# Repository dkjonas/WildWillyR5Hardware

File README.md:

Schematic and board layout for the R5 version of my robot.

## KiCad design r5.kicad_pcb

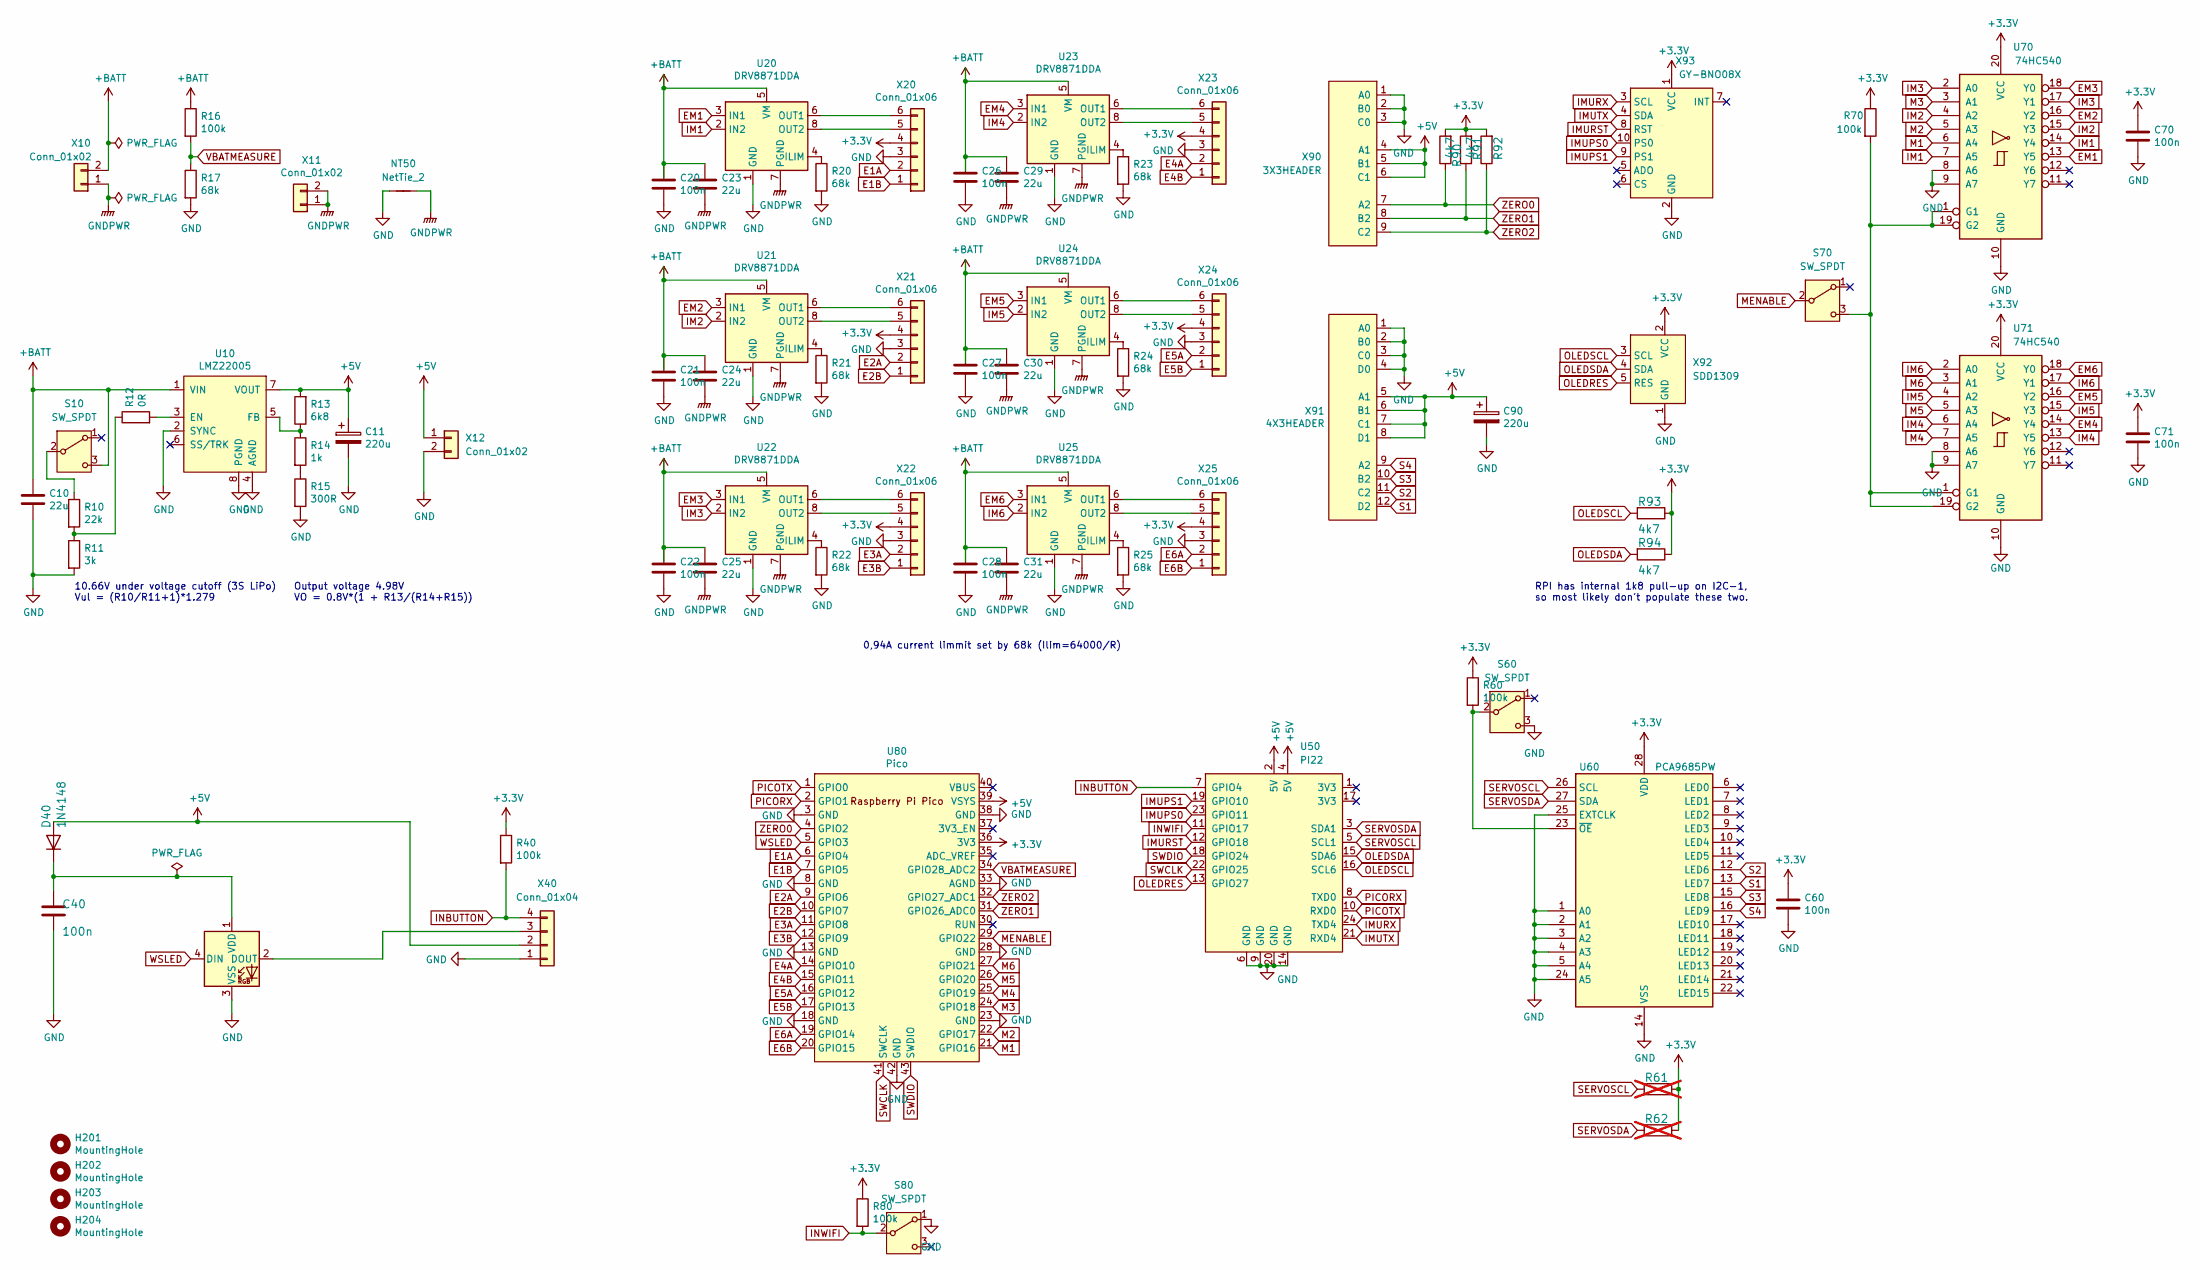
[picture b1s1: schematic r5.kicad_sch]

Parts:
C10, C23, C24, C25, C29, C30, C31: 22u; C_1206_3216Metric; LCSC Part # C12891
C11, C90: 220u; CP_Elec_6.3x7.7; LCSC Part # C970695
C20, C21, C22, C26, C27, C28, C40, C60, C70, C71: 100n; C_0805_2012Metric; LCSC Part # C49678
D40: 1N4148; D_SOD-323; LCSC Part # C2128
D41: WS2812B5050; LED_WS2812B_PLCC4_5.0x5.0mm_P3.2mm
H201, H202, H203, H204: MountingHole; MountingHole_3.2mm_M3
NT50: NetTie_2; NetTie-2_SMD_Pad2.0mm
R10: 22k; R_0805_2012Metric; LCSC Part # C17560
R11: 3k; R_0805_2012Metric; LCSC Part # C17661
R12: 0R; R_0805_2012Metric; LCSC Part # C17477
R13: 6k8; R_0805_2012Metric; LCSC Part # C17772
R14: 1k; R_0805_2012Metric; LCSC Part # C17513
R15: 300R; R_0805_2012Metric; LCSC Part # C17617
R16, R40, R60, R70, R80: 100k; R_0805_2012Metric; LCSC Part # C149504
R17, R20, R21, R22, R23, R24, R25: 68k; R_0805_2012Metric; LCSC Part # C17801
R61, R62: R_0805_2012Metric; not fitted
R90, R91, R92, R93, R94: 4k7; R_0805_2012Metric; LCSC Part # C17673
S10, S60, S70, S80: SW_SPDT; SW_Slide_1P2T_CK_OS102011MS2Q
U10: LMZ22005; 7TO-PMOD; LCSC Part # C2865843
U20, U21, U22, U23, U24, U25: DRV8871DDA; Texas_HTSOP-8-1EP_3.9x4.9mm_P1.27mm_EP2.95x4.9mm_Mask2.4x3.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; JLCPCB Rotation Offset -90
U50: PI22; PinSocket_2x12_P2.54mm_Vertical
U60: PCA9685PW; TSSOP-28_4.4x9.7mm_P0.65mm; LCSC Part # C2678753
U70, U71: 74HC540; TSSOP-20_4.4x6.5mm_P0.65mm; LCSC Part # C2682166
U80: Pico; RaspberryPiPico_SMD
X10: Conn_01x02; AMASS_XT60PW-M
X11: Conn_01x02; PinHeader_1x02_P2.54mm_Vertical
X12: Conn_01x02; JST_PH_B2B-PH-K_1x02_P2.00mm_Vertical
X20, X21, X22, X23, X24, X25: Conn_01x06; JST_PH_B6B-PH-K_1x06_P2.00mm_Vertical
X40: Conn_01x04; PinHeader_1x04_P2.54mm_Vertical
X90: 3X3HEADER; PinHeader_3x03_P2.54mm_Vertical
X91: 4X3HEADER; PinHeader_3x04_P2.54mm_Vertical
X92: SDD1309; PinHeader_1x05_P2.54mm_Vertical
X93: GY-BNO08X

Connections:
+3.3V: C60.1, C70.1, C71.1, R40.1, R60.1, R61.1, R62.1, R70.1, R80.1, R90.2, R91.2, R92.2, R93.1, R94.1, U60.28 (VDD), U70.20 (VCC), U71.20 (VCC), U80.36 (3V3), X20.4, X21.4, X22.4, X23.4, X24.4, X25.4, X92.2 (VCC), X93.1 (VCC)
+5V: C11.1, C90.1, D40.2 (A), R13.2, U10.7 (VOUT), U50.2 (5V), U50.4 (5V), U80.39 (VSYS), X12.1, X40.2, X90.4 (A1), X90.5 (B1), X90.6 (C1), X91.5 (A1), X91.6 (B1), X91.7 (C1), X91.8 (D1)
+BATT: C10.1, C20.1, C21.1, C22.1, C23.1, C24.1, C25.1, C26.1, C27.1, C28.1, C29.1, C30.1, C31.1, R16.1, S10.3 (C), U10.1 (VIN), U20.5 (VM), U21.5 (VM), U22.5 (VM), U23.5 (VM), U24.5 (VM), U25.5 (VM), X10.2
E1A: U80.6 (GPIO4), X20.2
E1B: U80.7 (GPIO5), X20.1
E2A: U80.9 (GPIO6), X21.2
E2B: U80.10 (GPIO7), X21.1
E3A: U80.11 (GPIO8), X22.2
E3B: U80.12 (GPIO9), X22.1
E4A: U80.14 (GPIO10), X23.2
E4B: U80.15 (GPIO11), X23.1
E5A: U80.16 (GPIO12), X24.2
E5B: U80.17 (GPIO13), X24.1
E6A: U80.19 (GPIO14), X25.2
E6B: U80.20 (GPIO15), X25.1
EM1: U20.3 (IN1), U70.13 (Y5)
EM2: U21.3 (IN1), U70.16 (Y2)
EM3: U22.3 (IN1), U70.18 (Y0)
EM4: U23.3 (IN1), U71.14 (Y4)
EM5: U24.3 (IN1), U71.16 (Y2)
EM6: U25.3 (IN1), U71.18 (Y0)
GND: C10.2, C11.2, C20.2, C21.2, C22.2, C26.2, C27.2, C28.2, C40.2, C60.2, C70.2, C71.2, C90.2, D41.3 (VSS), NT50.1, R11.2, R15.2, R17.2, R20.2, R21.2, R22.2, R23.2, R24.2, R25.2, S60.3 (C), S80.1 (A), U10.2 (SYNC), U10.4 (AGND), U10.8 (PGND), U20.1 (GND), U20.9 (GND), U21.1 (GND), U21.9 (GND), U22.1 (GND), U22.9 (GND), U23.1 (GND), U23.9 (GND), U24.1 (GND), U24.9 (GND), U25.1 (GND), U25.9 (GND), U50.6 (GND), U50.9 (GND), U50.14 (GND), U50.20 (GND), U60.1 (A0), U60.2 (A1), U60.3 (A2), U60.4 (A3), U60.5 (A4), U60.14 (VSS), U60.24 (A5), U60.25 (EXTCLK), U70.8 (A6), U70.9 (A7), U70.10 (GND), U71.8 (A6), U71.9 (A7), U71.10 (GND), U80.3 (GND), U80.8 (GND), U80.13 (GND), U80.18 (GND), U80.23 (GND), U80.28 (GND), U80.33 (AGND), U80.38 (GND), U80.42 (GND), X12.2, X20.3, X21.3, X22.3, X23.3, X24.3, X25.3, X40.1, X90.1 (A0), X90.2 (B0), X90.3 (C0), X91.1 (A0), X91.2 (B0), X91.3 (C0), X91.4 (D0), X92.1 (GND), X93.2 (GND)
GNDPWR: C23.2, C24.2, C25.2, C29.2, C30.2, C31.2, NT50.2, U20.7 (PGND), U21.7 (PGND), U22.7 (PGND), U23.7 (PGND), U24.7 (PGND), U25.7 (PGND), X10.1, X11.1, X11.2
IM1: U20.2 (IN2), U70.7 (A5), U70.14 (Y4)
IM2: U21.2 (IN2), U70.4 (A2), U70.15 (Y3)
IM3: U22.2 (IN2), U70.2 (A0), U70.17 (Y1)
IM4: U23.2 (IN2), U71.6 (A4), U71.13 (Y5)
IM5: U24.2 (IN2), U71.4 (A2), U71.15 (Y3)
IM6: U25.2 (IN2), U71.2 (A0), U71.17 (Y1)
IMUPS0: U50.23 (GPIO11), X93.10 (PS0)
IMUPS1: U50.19 (GPIO10), X93.9 (PS1)
IMURST: U50.12 (GPIO18), X93.8 (RST)
IMURX: U50.24 (TXD4), X93.3 (SCL)
IMUTX: U50.21 (RXD4), X93.4 (SDA)
INBUTTON: R40.2, U50.7 (GPIO4), X40.4
INWIFI: R80.2, S80.2 (B), U50.11 (GPIO17)
M1: U70.6 (A4), U80.21 (GPIO16)
M2: U70.5 (A3), U80.22 (GPIO17)
M3: U70.3 (A1), U80.24 (GPIO18)
M4: U71.7 (A5), U80.25 (GPIO19)
M5: U71.5 (A3), U80.26 (GPIO20)
M6: U71.3 (A1), U80.27 (GPIO21)
MENABLE: S70.2 (B), U80.29 (GPIO22)
unnamed: C40.1, D40.1 (K), D41.1 (VDD)
unnamed: D41.2 (DOUT), X40.3
unnamed: R10.2, R11.1, R12.1
unnamed: R14.2, R15.1
unnamed: R10.1, S10.2 (B)
unnamed: R60.2, S60.2 (B), U60.23 (~OE)
unnamed: R70.2, S70.3 (C), U70.1 (G1), U70.19 (G2), U71.1 (G1), U71.19 (G2)
unnamed: R12.2, U10.3 (EN)
unnamed: R13.1, R14.1, U10.5 (FB)
unnamed: R20.1, U20.4 (ILIM)
unnamed: U20.6 (OUT1), X20.6
unnamed: U20.8 (OUT2), X20.5
unnamed: R21.1, U21.4 (ILIM)
unnamed: U21.6 (OUT1), X21.6
unnamed: U21.8 (OUT2), X21.5
unnamed: R22.1, U22.4 (ILIM)
unnamed: U22.6 (OUT1), X22.6
unnamed: U22.8 (OUT2), X22.5
unnamed: R23.1, U23.4 (ILIM)
unnamed: U23.6 (OUT1), X23.6
unnamed: U23.8 (OUT2), X23.5
unnamed: R24.1, U24.4 (ILIM)
unnamed: U24.6 (OUT1), X24.6
unnamed: U24.8 (OUT2), X24.5
unnamed: R25.1, U25.4 (ILIM)
unnamed: U25.6 (OUT1), X25.6
unnamed: U25.8 (OUT2), X25.5
OLEDRES: U50.13 (GPIO27), X92.5 (RES)
OLEDSCL: R93.2, U50.16 (SCL6), X92.3 (SCL)
OLEDSDA: R94.2, U50.15 (SDA6), X92.4 (SDA)
PICORX: U50.8 (TXD0), U80.2 (GPIO1)
PICOTX: U50.10 (RXD0), U80.1 (GPIO0)
S1: U60.13 (LED7), X91.12 (D2)
S2: U60.12 (LED6), X91.11 (C2)
S3: U60.15 (LED8), X91.10 (B2)
S4: U60.16 (LED9), X91.9 (A2)
SERVOSCL: R61.2, U50.5 (SCL1), U60.26 (SCL)
SERVOSDA: R62.2, U50.3 (SDA1), U60.27 (SDA)
SWCLK: U50.22 (GPIO25), U80.41 (SWCLK)
SWDIO: U50.18 (GPIO24), U80.43 (SWDIO)
VBATMEASURE: R16.2, R17.1, U80.34 (GPIO28_ADC2)
WSLED: D41.4 (DIN), U80.5 (GPIO3)
ZERO0: R90.1, U80.4 (GPIO2), X90.7 (A2)
ZERO1: R91.1, U80.31 (GPIO26_ADC0), X90.8 (B2)
ZERO2: R92.1, U80.32 (GPIO27_ADC1), X90.9 (C2)

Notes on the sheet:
0,94A current limmit set by 68k (Ilim=64000/R)
Output voltage 4.98V VO = 0.8V*(1 + R13/(R14+R15))
10.66V under voltage cutoff (3S LiPo) Vul = (R10/R11+1)*1.279
RPI has internal 1k8 pull-up on I2C-1, so most likely don't populate these two.

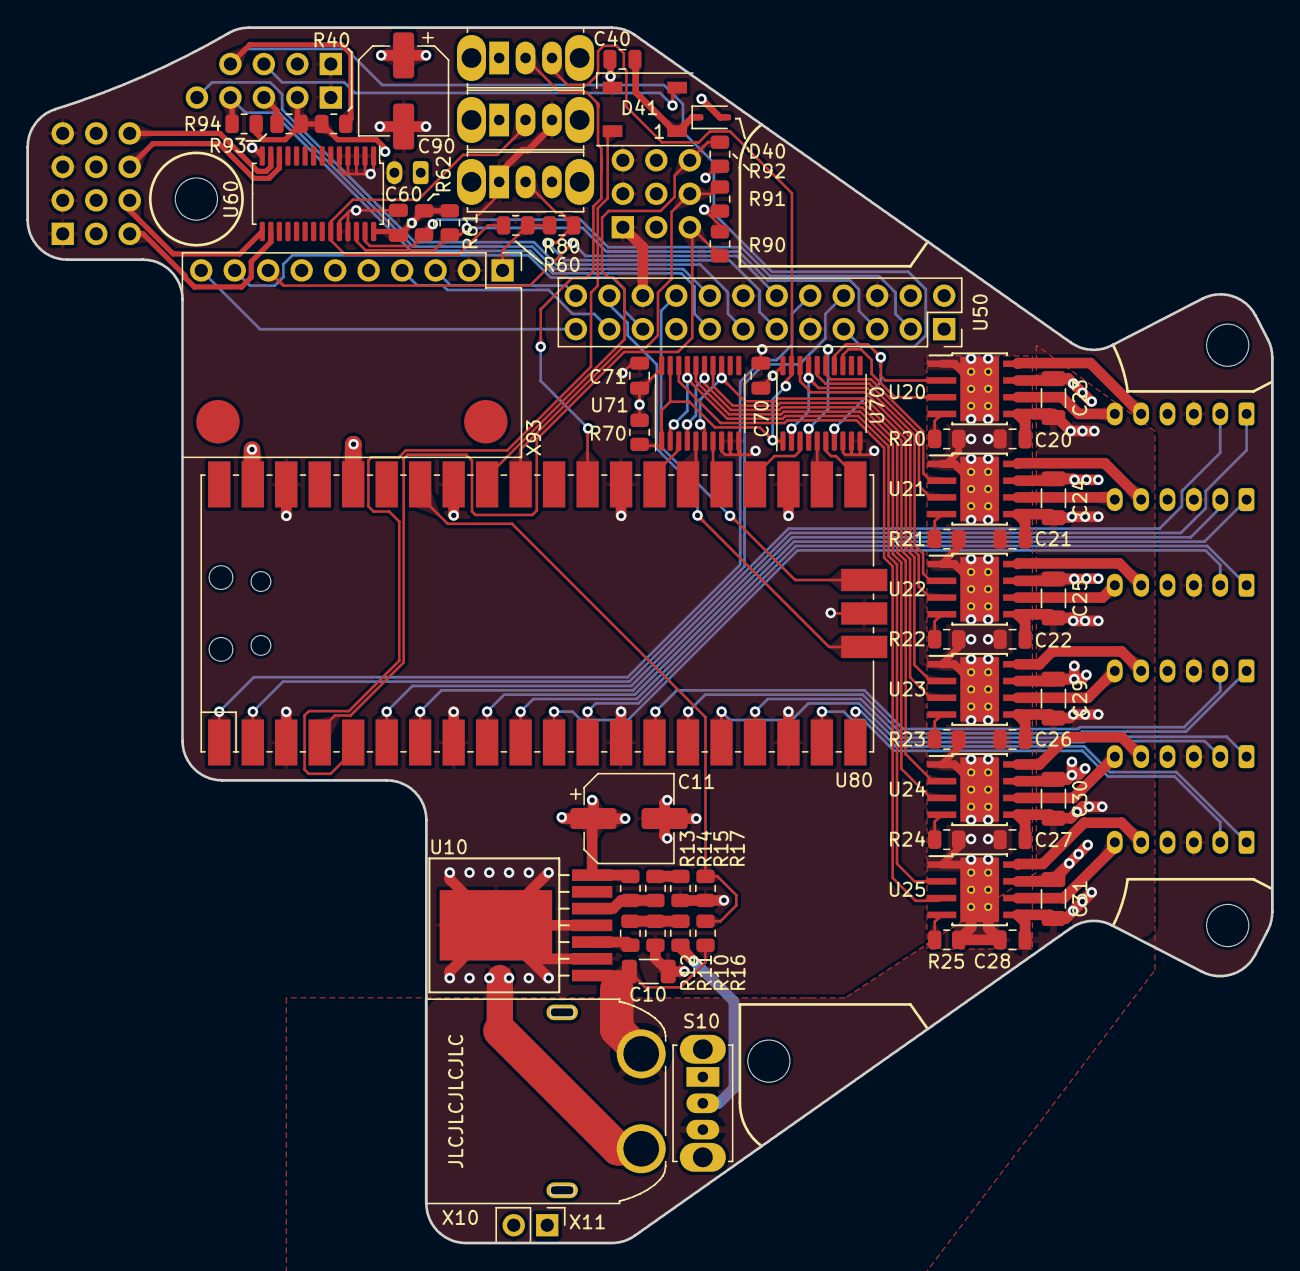
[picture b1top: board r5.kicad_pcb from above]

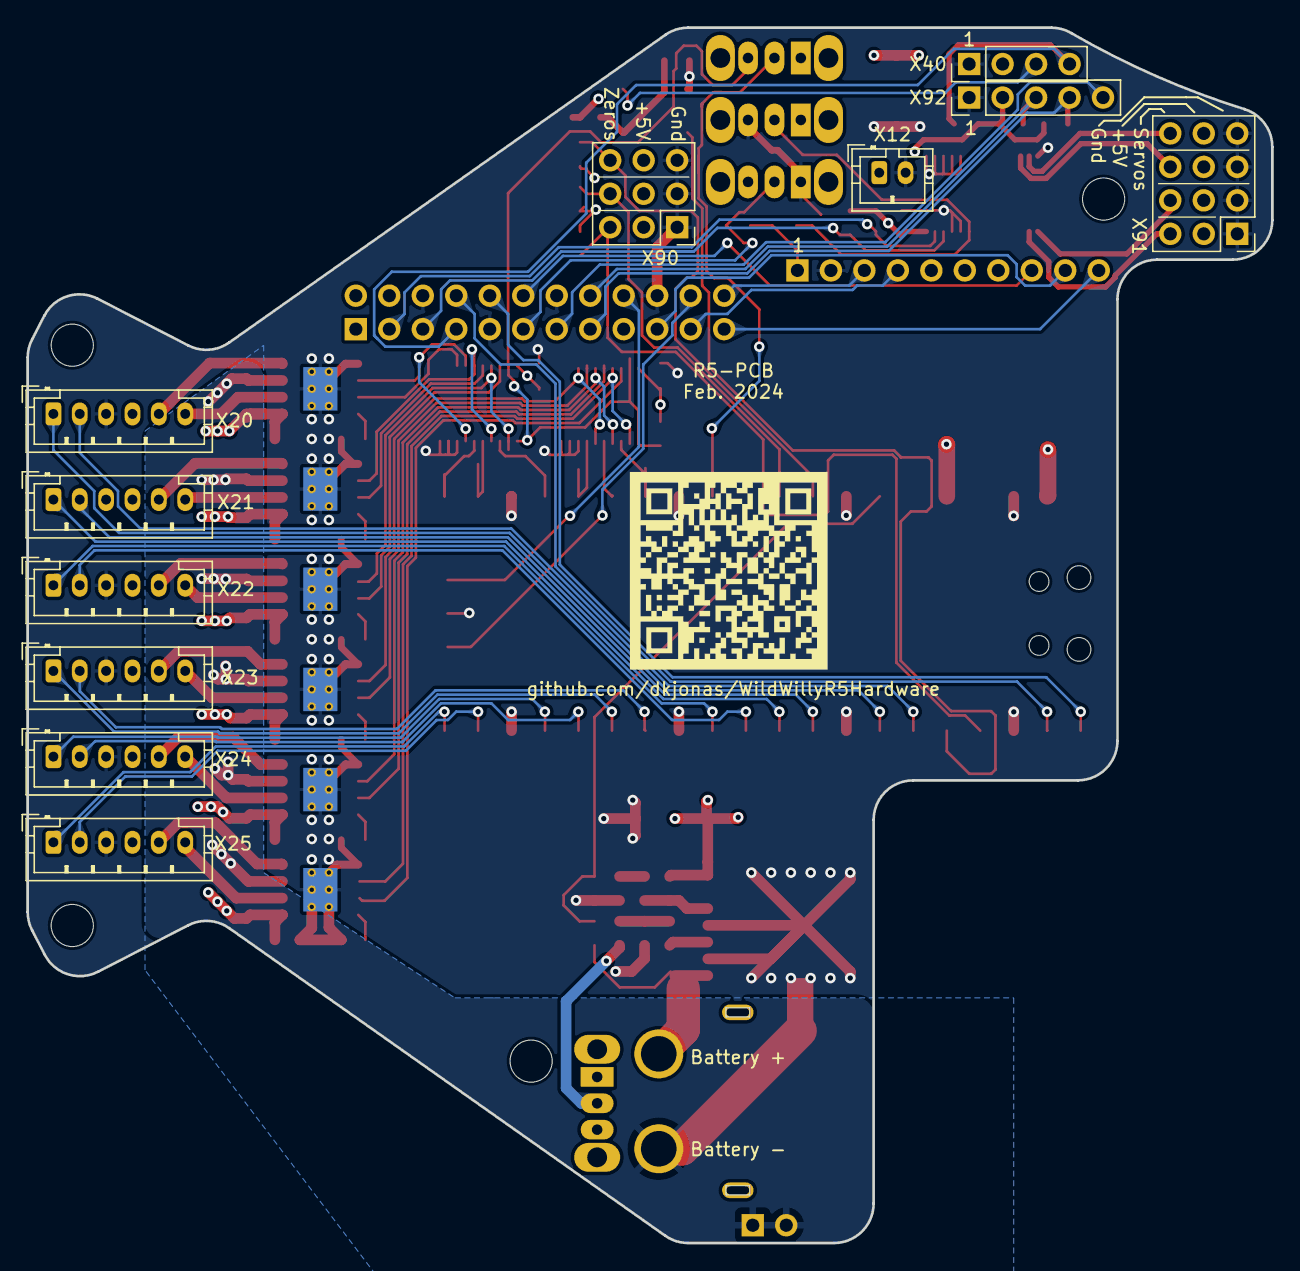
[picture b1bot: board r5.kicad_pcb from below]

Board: 4 copper layers, 94.4 x 92.2 mm, 81 parts (11 on the bottom side), 88 nets.

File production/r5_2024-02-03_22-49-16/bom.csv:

Designator,Footprint,Quantity,Value,LCSC Part #
"C10, C23, C24, C25, C29, C30, C31",1206,7,22u,C12891
"C11, C90",CP_Elec_6.3x7.7,2,220u,C970695
"C20, C21, C22, C26, C27, C28, C40, C60, C70, C71",0805,10,100n,C49678
D40,D_SOD-323,1,1N4148,C2128
R10,0805,1,22k,C17560
R11,0805,1,3k,C17661
R12,0805,1,0R,C17477
R13,0805,1,6k8,C17772
R14,0805,1,1k,C17513
R15,0805,1,300R,C17617
"R16, R40, R60, R70, R80",0805,5,100k,C149504
"R17, R20, R21, R22, R23, R24, R25",0805,7,68k,C17801
"R90, R91, R92, R93, R94",0805,5,4k7,C17673
"U20, U21, U22, U23, U24, U25",Texas_HTSOP-8-1EP_3.9x4.9mm_P1.27mm_EP2.95x4.9mm_Mask2.4x3.1mm_ThermalVias,6,DRV8871DDA,C75864
U60,TSSOP-28_4.4x9.7mm_P0.65mm,1,PCA9685PW,C2678753
"U70, U71",TSSOP-20_4.4x6.5mm_P0.65mm,2,74HC540,C2682166

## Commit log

2024-01-24 Initial import of R5
2024-01-25 Disable git converting cr/lf
2024-01-25 Add JLCPCB design rules
2024-01-29 component placement
2024-01-29 positions
2024-01-29 start routing
2024-01-30 use 2 inverters
2024-01-30 routing
2024-01-30 routing continued
2024-01-31 routing done
2024-01-31 remove some DRC
2024-02-01 Silk cleanup
2024-02-03 board done
2024-02-03 Production files 2024-02-03
2024-02-06 minor schematic cleanup
2024-04-26 Render
